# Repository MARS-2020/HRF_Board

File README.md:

# HRF_Board
Heart rate sensor board

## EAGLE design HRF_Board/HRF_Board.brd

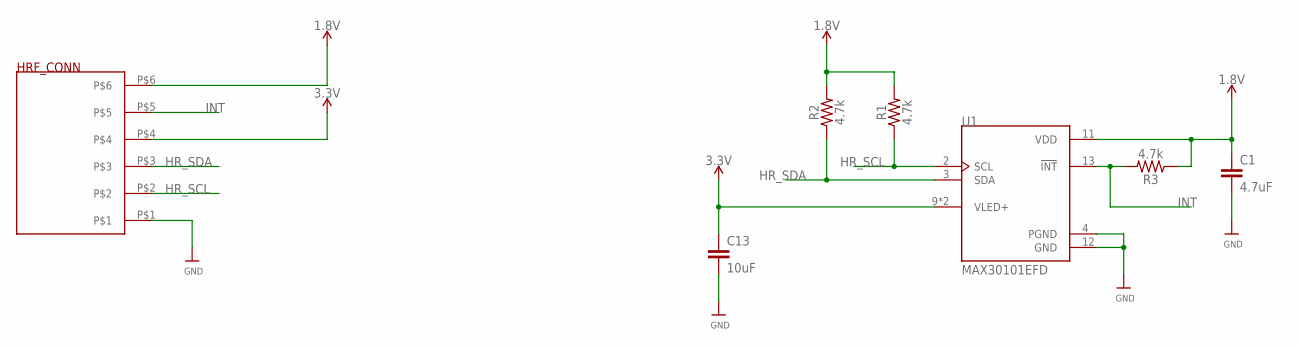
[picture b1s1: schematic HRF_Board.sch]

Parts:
C1: 4.7uF; 0603
C13: 10uF; 0603
R1, R2, R3: 4.7k; 0603
U1: MAX30101EFD; PSON80P560X330X165-14N
U$1: HRF_CONN

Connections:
1.8V: C1.1, R1.2, R2.2, R3.1, U1.11 (VDD), U$1.P$6
3.3V: C13.1, U1.9 (VLED+), U1.10 (VLED+), U$1.P$4
GND: C1.2, C13.2, U1.4 (PGND), U1.12 (GND), U$1.P$1
HR_SCL: R1.1, U1.2 (SCL), U$1.P$2
HR_SDA: R2.1, U1.3 (SDA), U$1.P$3
INT: R3.2, U1.13 (!INT), U$1.P$5

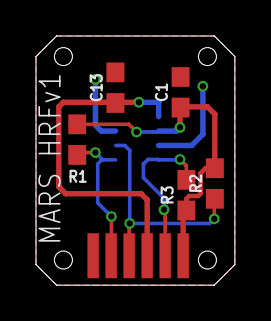
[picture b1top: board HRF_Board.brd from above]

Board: 2 copper layers, 11.0 x 13.8 mm, 7 parts (1 on the bottom side), 6 nets.

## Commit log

2020-02-12 Start
2020-02-12 Schematic work
2020-02-13 Things and stuff
2020-02-13 Fully routed
2020-02-13 DRC CHECK
2020-02-13 Board outline fixes and tented vias
2020-02-13 Silk Screen
2020-03-02 Rerouted with new connector and added full ground plane
2020-03-11 silkscreen

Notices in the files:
parts and their libraries:
SparkFun-Resistors: Licensing: Creative Commons ShareAlike 4.0 International - https://creativecommons.org/licenses/by-sa/4.0
microbuilder: This work is placed in the public domain, and may be freely used for commercial and non-commercial work with the following conditions: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
